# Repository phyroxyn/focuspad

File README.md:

# focuspad_v2

A compact 4×4 macropad for Windows productivity workflows (Fusion 360, Bambu Studio, Adobe Illustrator/Photoshop, DaVinci Resolve). It features two knobs: the **left knob is a push-button only** (purely for aesthetics), while the **right knob is a real rotary encoder** for volume control.

## Render

.png)
## PCB
### Schematic

### PCB Layout

## Case
The enclosure is designed as **five parts**:
- **Top cover** (protects the PCB; acrylic would look great).
- **Base** (with heat-set insert holes to mount the PCB and top cover).
- **Side cover** (hides the PCB ; would look great in milled aluminum).
- **Sub-base / stand** (tilts the macropad at an ergonomic angle).
- **Connector** (connects the base with the stand).

## Firmware
Firmware is written in QMK.
- Left knob: **push-button only** → Mute/Unmute.
- Right knob: **rotary encoder** → Volume Up/Down.
- The 12 keys are mapped to common Windows shortcuts.

QMK setup help:
- https://docs.qmk.fm/#/getting_started_build_tools 
- https://docs.qmk.fm/#/getting_started_make_guide 
- https://youtu.be/BcXycScePHM?t=360&si=u64MpJI-V58_fIYx

## Bill of Materials (BOM)
| Item | Qty | Notes / Part |
|------|-----|--------------|
| [Seeed Studio XIAO RP2040](https://wiki.seeedstudio.com/XIAO-RP2040/) (through-hole) | 1 | Main MCU |
|MX brown switches| 12 | 4×4 grid, corners missing |
| Keycaps | 12 | [**low profile**, black](https://shop.beekeeb.com/products/smolo-low-profile-keycap) |
| Rotary encoder (EC11, 15mm)(w. **push putton**) | 2 | Right&left knob (rotary) |
| Diodes (1N4148, through-hole) | 13 | For matrix and left encoder|
| Rotary encoder caps|2|Cool locking and **black**|
|(3D printed parts) | 5|Black Petg/ aluminium & plexiglas|
| M3 heat-set inserts (M3×5×4) | 4 | Case mounting |
| M3 screws | 4 | Case mounting |
|PCB|1|Black PCB(Solder mask)|

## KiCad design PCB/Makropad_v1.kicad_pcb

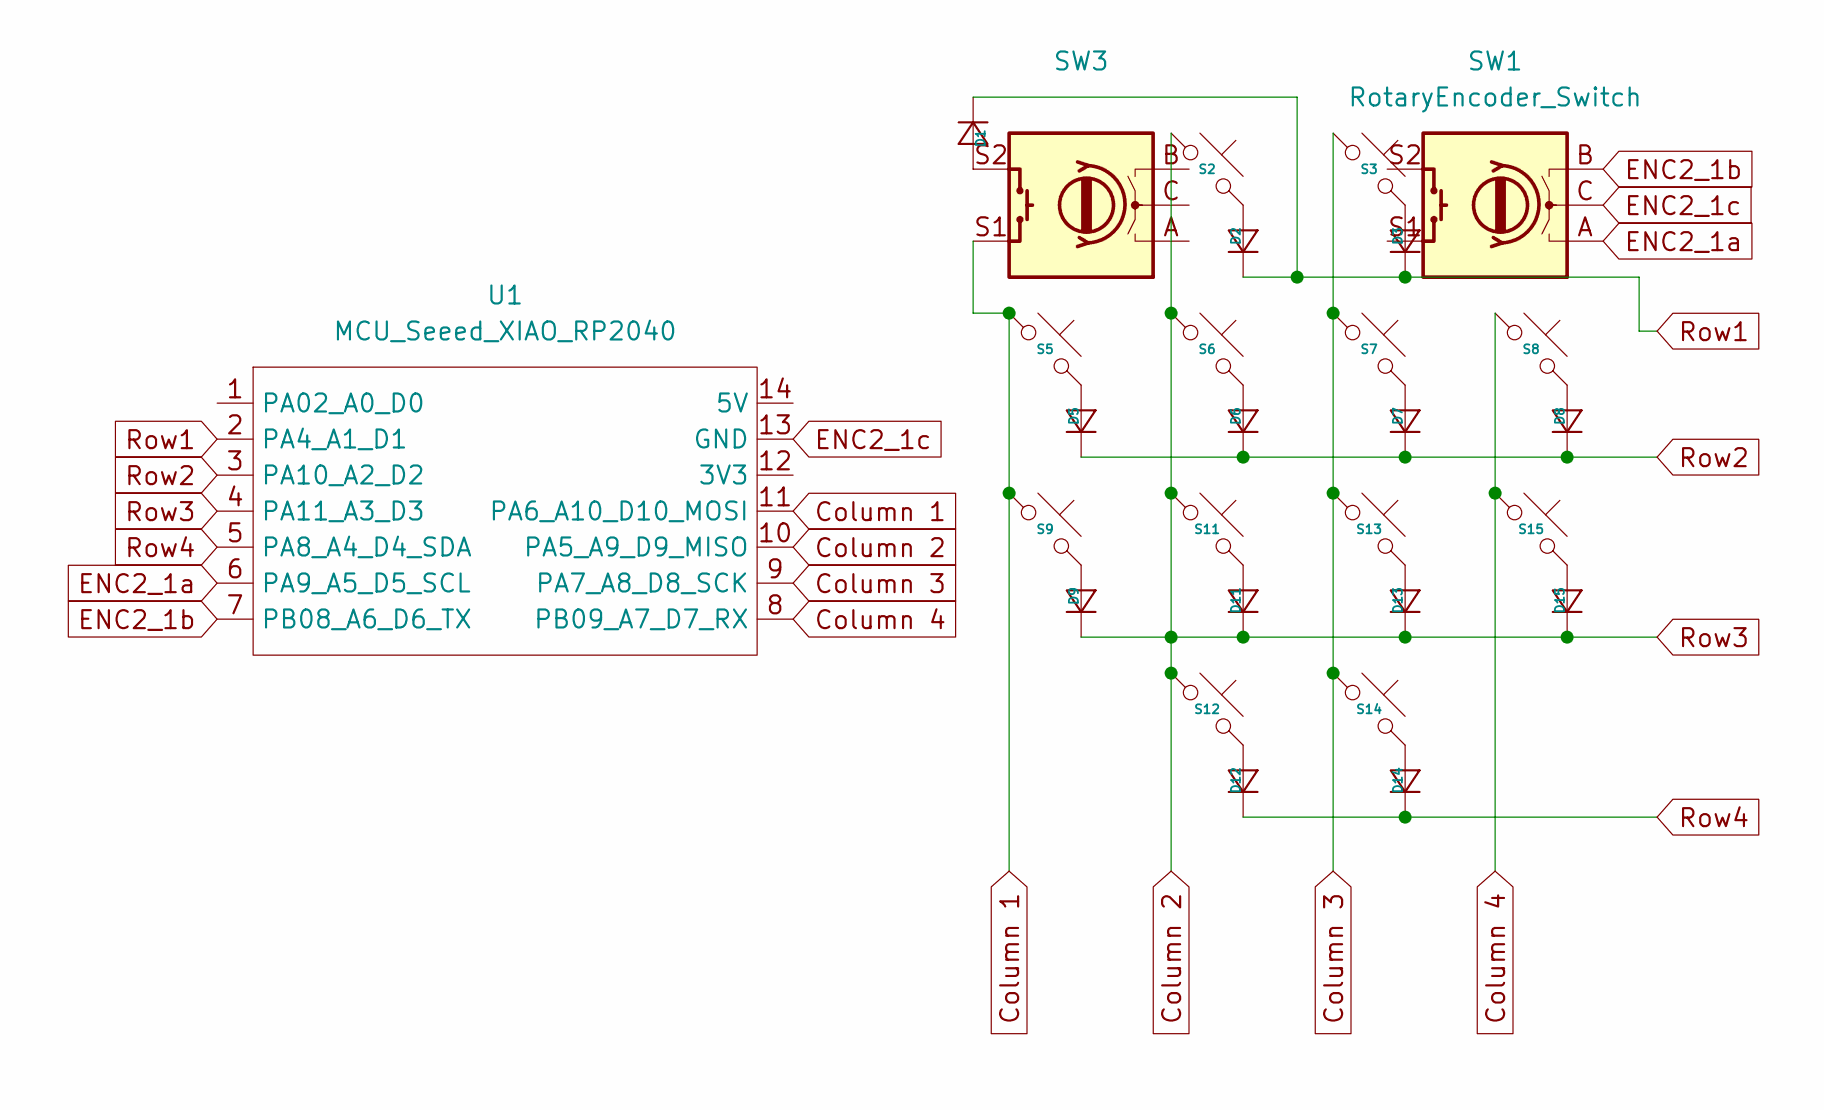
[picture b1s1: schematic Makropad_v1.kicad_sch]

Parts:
D1, D2, D3, D5, D6, D7, D8, D9, D11, D12, D13, D14, D15: D_DO-35_SOD27_P7.62mm_Horizontal
S2, S3, S5, S6, S7, S8, S9, S11, S12, S13, S14, S15: MX_Solder_1.00u
SW1, SW3: RotaryEncoder_Switch; RotaryEncoder_Alps_EC11E-Switch_Vertical_H20mm
U1: MCU_Seeed_XIAO_RP2040; Seeed_XIAO_RP2040

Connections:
Column 1: S5.1, S9.1, SW3.S1, U1.11 (PA6_A10_D10_MOSI)
Column 2: D9.1 (K), D11.1 (K), D13.1 (K), D15.1 (K), S2.1, S6.1, S11.1, S12.1, U1.4 (PA11_A3_D3), U1.10 (PA5_A9_D9_MISO)
Column 3: S3.1, S7.1, S13.1, S14.1, U1.9 (PA7_A8_D8_SCK)
Column 4: S8.1, S15.1, U1.8 (PB09_A7_D7_RX)
ENC2_1a: SW1.A, U1.6 (PA9_A5_D5_SCL)
ENC2_1b: SW1.B, U1.7 (PB08_A6_D6_TX)
ENC2_1c: SW1.C, U1.13 (GND)
unnamed: D1.2 (A), SW3.S2
unnamed: D2.2 (A), S2.2
unnamed: D3.2 (A), S3.2
unnamed: D5.2 (A), S5.2
unnamed: D6.2 (A), S6.2
unnamed: D7.2 (A), S7.2
unnamed: D8.2 (A), S8.2
unnamed: D9.2 (A), S9.2
unnamed: D11.2 (A), S11.2
unnamed: D12.2 (A), S12.2
unnamed: D13.2 (A), S13.2
unnamed: D14.2 (A), S14.2
unnamed: D15.2 (A), S15.2
Row1: D1.1 (K), D2.1 (K), D3.1 (K), U1.2 (PA4_A1_D1)
Row2: D5.1 (K), D6.1 (K), D7.1 (K), D8.1 (K), U1.3 (PA10_A2_D2)
Row4: D12.1 (K), D14.1 (K), U1.5 (PA8_A4_D4_SDA)

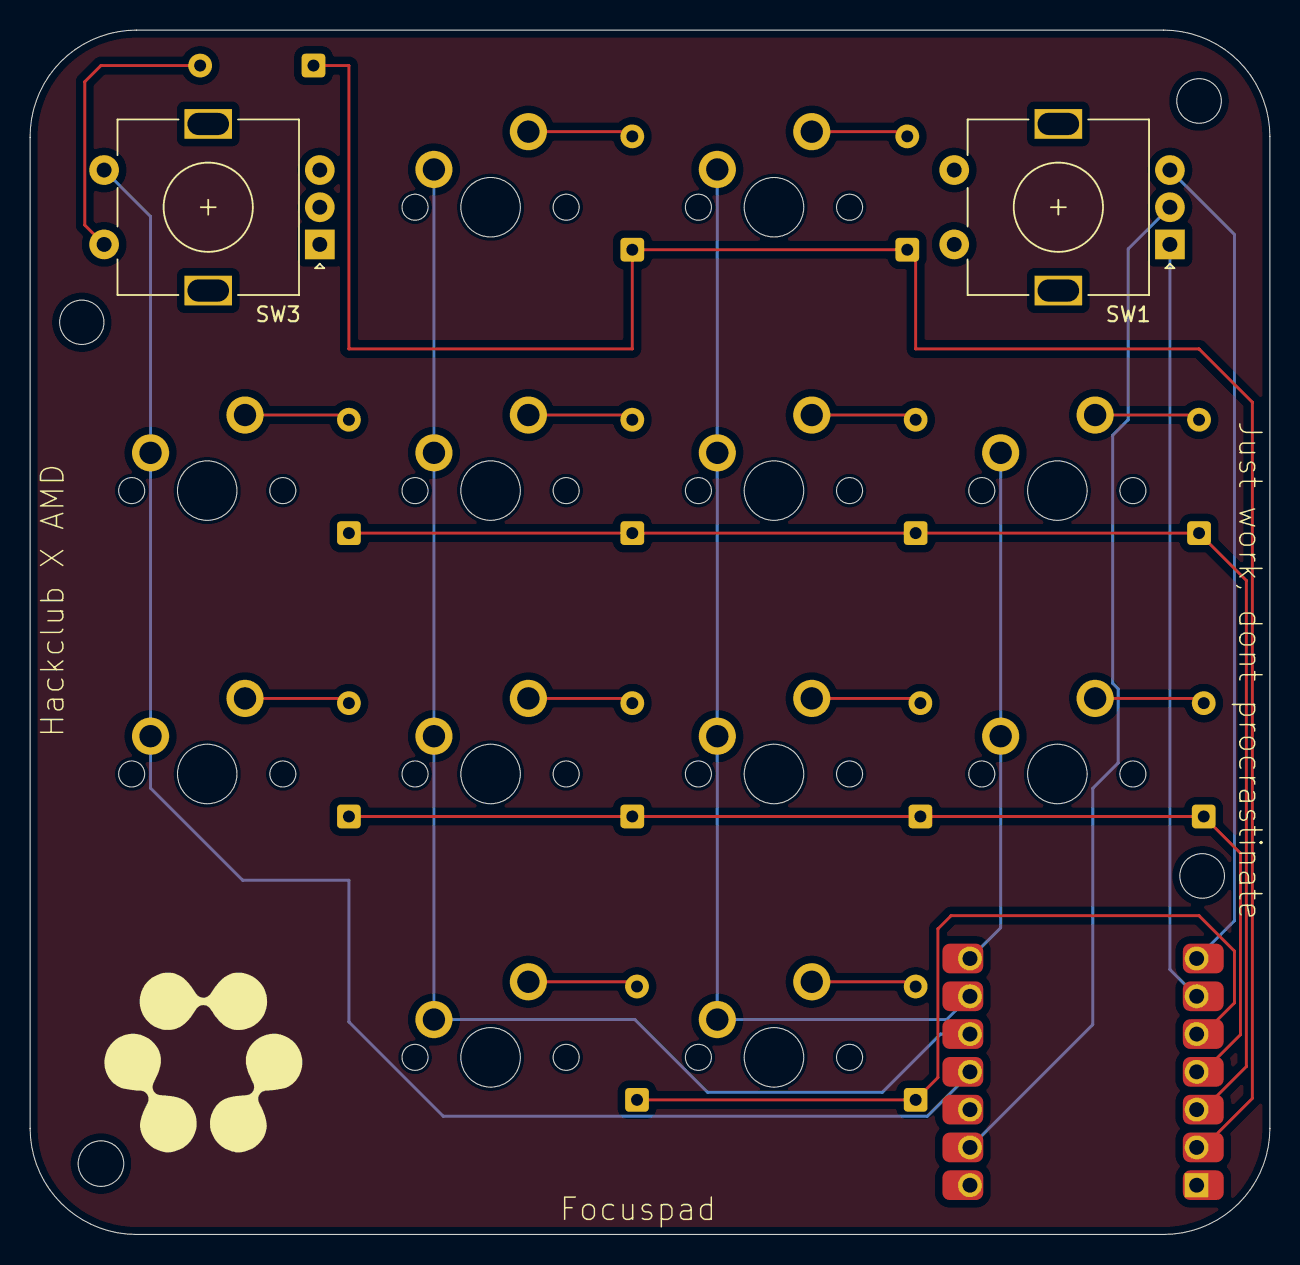
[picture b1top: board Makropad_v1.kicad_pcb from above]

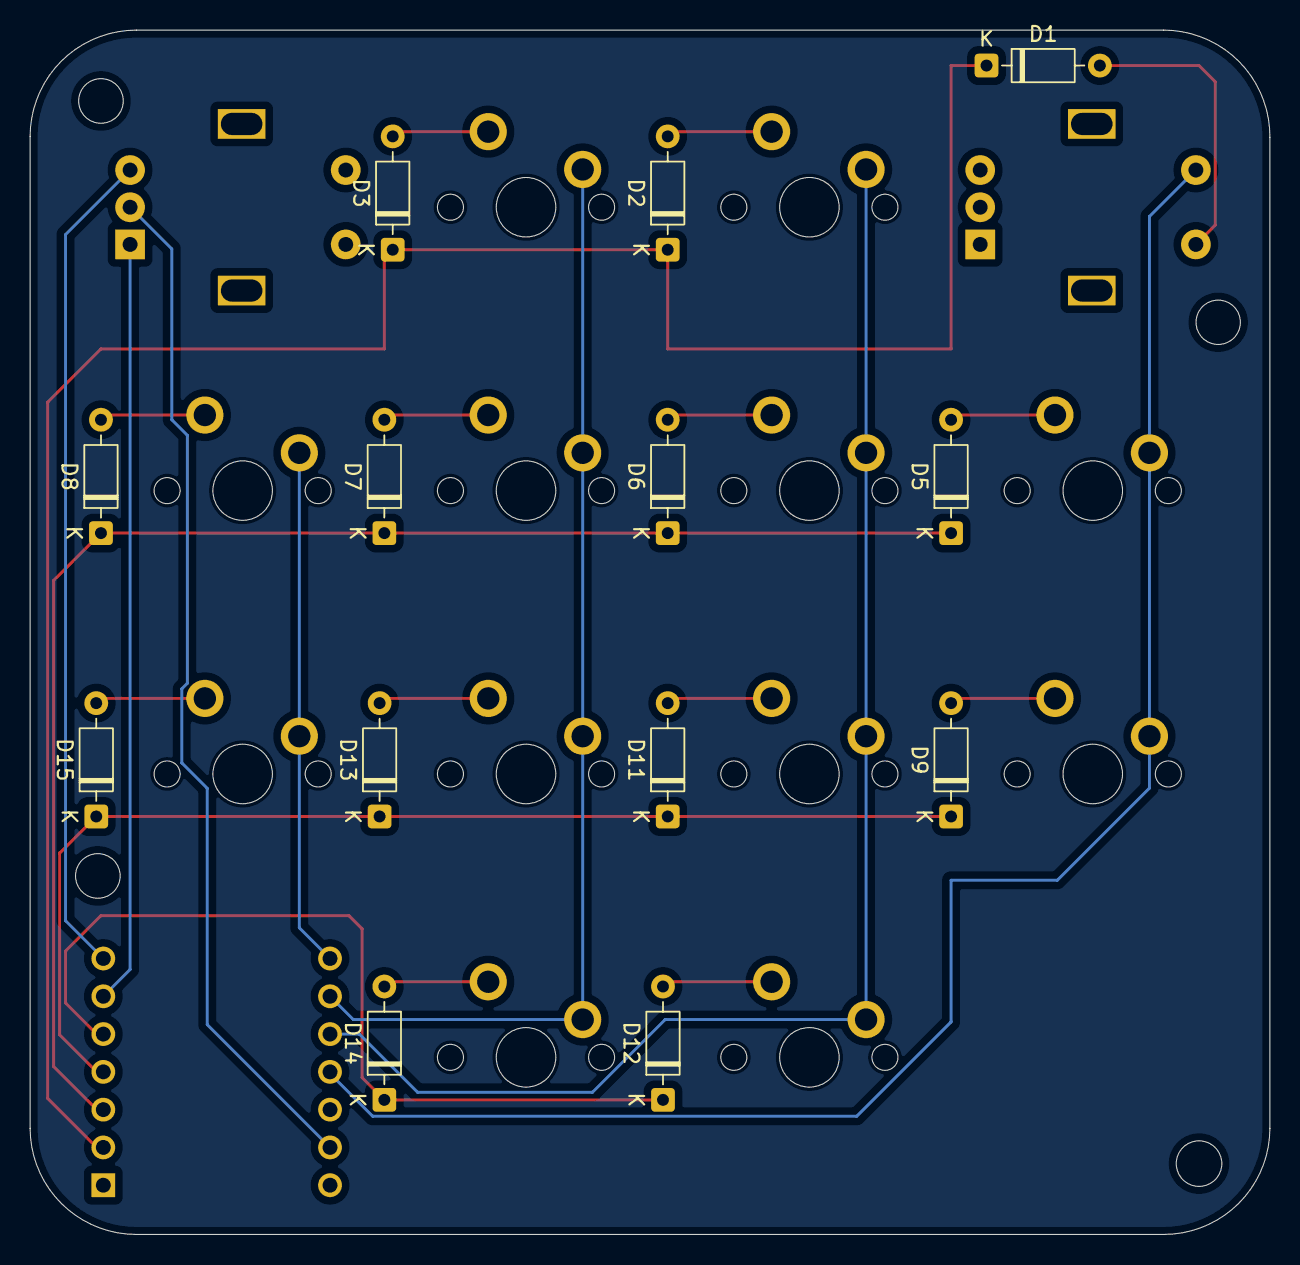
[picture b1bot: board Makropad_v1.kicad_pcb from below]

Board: 2 copper layers, 83.3 x 81.0 mm, 28 parts (13 on the bottom side), 23 nets.

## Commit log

2025-12-29 Add link to Seeed Studio XIAO RP2040 in BOM
    For those who want to explore more details
2025-12-29 Adding Links to readme
2026-01-03 Update README.md
    Change back from choc Style switches to MX Style switches after getting HCB Mail with infos
